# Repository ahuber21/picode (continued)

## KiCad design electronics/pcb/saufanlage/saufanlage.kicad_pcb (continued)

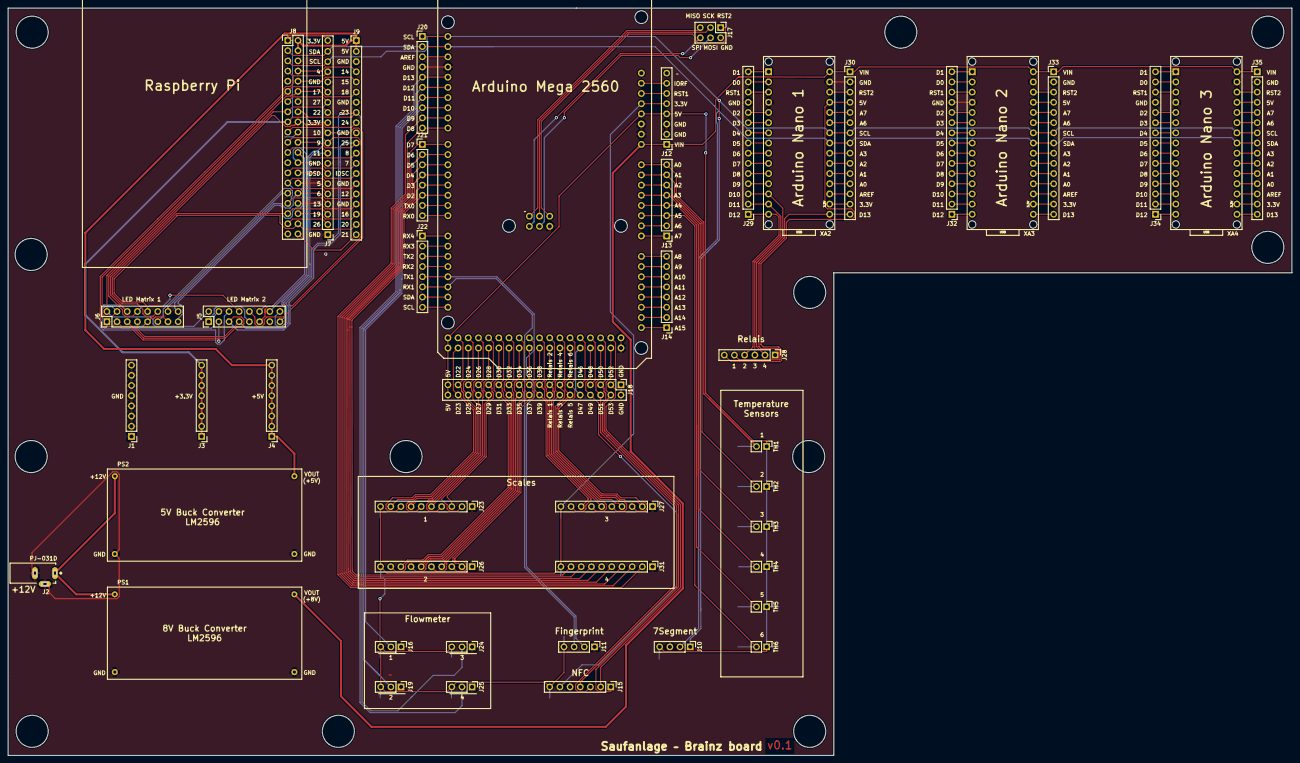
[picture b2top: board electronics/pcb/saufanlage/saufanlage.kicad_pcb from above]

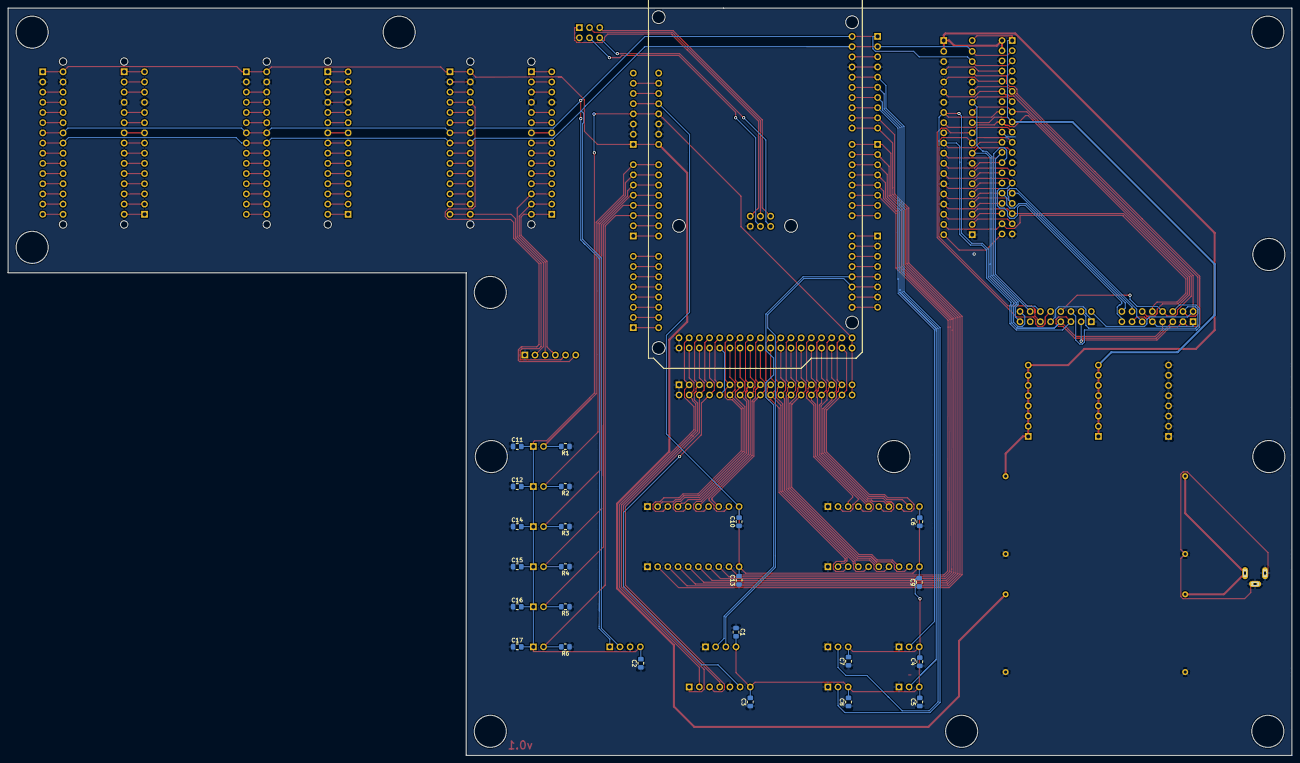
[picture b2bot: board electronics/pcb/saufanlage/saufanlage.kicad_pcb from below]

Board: 2 copper layers, 320.3 x 186.4 mm, 70 parts (24 on the bottom side), 188 nets.

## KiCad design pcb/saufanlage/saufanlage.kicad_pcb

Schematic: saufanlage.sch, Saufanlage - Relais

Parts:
C1: C; C_2220_5650Metric_Pad1.97x5.40mm_HandSolder
C2: C; C_1206_3216Metric_Pad1.42x1.75mm_HandSolder
C3: C; C_0805_2012Metric_Pad1.15x1.40mm_HandSolder
C4: C; C_1812_4532Metric_Pad1.30x3.40mm_HandSolder
D1: D_Schottky; D_SOT-23_ANK
D2: LED; LED_0805_2012Metric_Pad1.15x1.40mm_HandSolder
J1: Screw_Terminal_01x02; TerminalBlock_Altech_AK300-2_P5.00mm
J2: Conn_02x06_Odd_Even; IDC-Header_2x06_P2.54mm_Vertical
J3: Conn_01x02_Female; PinSocket_1x02_P2.54mm_Vertical
J4: Conn_01x07_Male; JST_EH_B7B-EH-A_1x07_P2.50mm_Vertical
J5: Conn_02x20_Odd_Even; PinSocket_2x20_P2.54mm_Vertical
J6: Conn_01x06_Female; PinSocket_1x06_P2.54mm_Vertical
J7, J8, J9, J10: Conn_01x03_Male; FanPinHeader_1x03_P2.54mm_Vertical
L1: L; L_12x12mm_H8mm
R1, R2, R3, R4, R5, R6, R7, R8, R9, R10, R11: R; R_0805_2012Metric_Pad1.15x1.40mm_HandSolder
SW1: SW_Push; SW_SPST_CK_RS282G05A3
U1: BD9G341EFJ; HTSOP-8-1EP_3.9x4.9mm_P1.27mm_EP2.4x3.2mm_ThermalVias
U2: 74HC595; DIP-16_W7.62mm_Socket

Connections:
+3V3: J4.2, J4.6, J5.1, J7.3, J8.3, J9.3, J10.3
+5V: C4.1, J5.2, J6.1, L1.2, R6.1, R9.1, SW1.1, U2.16
+12V: C1.1, J1.2, R1.1, U1.8 (VCC)
GND: C1.2, C4.2, D1.2 (A), D2.1, J1.1, J3.2, J4.5, J5.9, J6.6, J7.1, J8.1, J9.1, J10.1, R2.2, R3.2, R4.2, R5.1, R7.2, R8.1, R10.1, R11.1, U1.2 (GND), U2.8, U2.13
unnamed: C2.1, U1.3 (VC)
unnamed: C2.2, R4.1
unnamed: C3.1, U1.7 (BST)
unnamed: C3.2, D1.1 (K), L1.1, U1.1 (LX)
unnamed: D2.2, R9.2
unnamed: J2.1, U2.4
unnamed: J2.2, U2.3
unnamed: J2.3, U2.7
unnamed: J2.4, U2.2
unnamed: J2.5, U2.6
unnamed: J2.6, R8.2
unnamed: J2.7, U2.1
unnamed: J2.8, R10.2
unnamed: J2.9, R5.2
unnamed: J2.10, U2.5
unnamed: J2.11, U2.15
unnamed: J2.12, R11.2
unnamed: J3.1, SW1.2
unnamed: J4.3, J5.10
unnamed: J4.4, J5.8
unnamed: J5.16, U2.11
unnamed: J5.18, U2.12
unnamed: J5.22, U2.14
unnamed: J5.32, J6.2
unnamed: J5.33, J9.2
unnamed: J5.35, J8.2
unnamed: J5.36, J6.3
unnamed: J5.37, J7.2
unnamed: J5.38, J6.4
unnamed: J5.40, J6.5
unnamed: J5.31, J10.2
unnamed: R1.2, R2.1, U1.6 (EN)
unnamed: R3.1, U1.5 (RT)
unnamed: R6.2, R7.1, U1.4 (FB)

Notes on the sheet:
Buck Converter
Flowmeter-connection
Relais-Connection
Raspberry - reset
Fingerprint Connection
7-seg anzeige

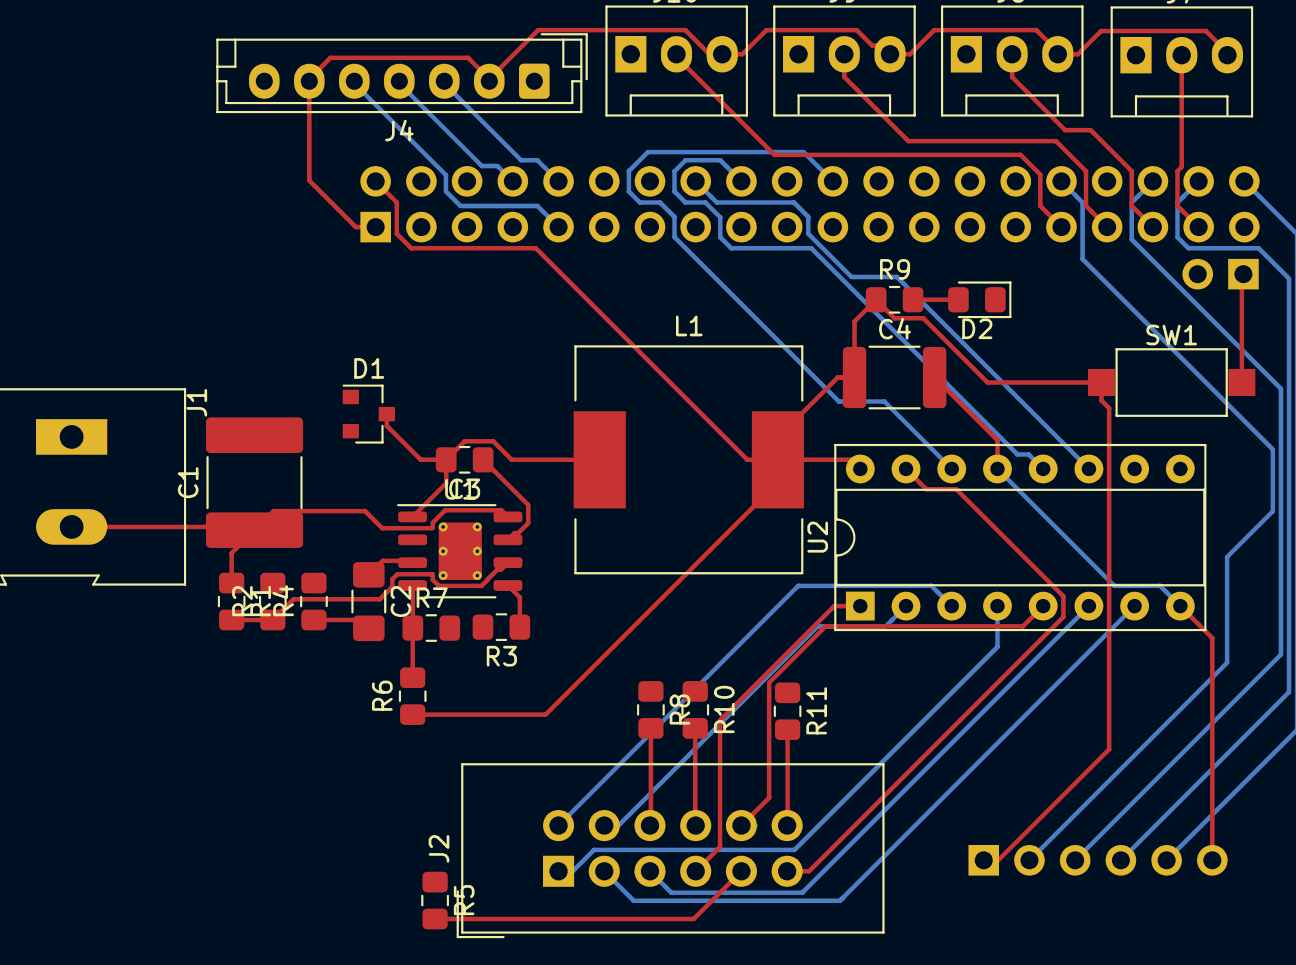
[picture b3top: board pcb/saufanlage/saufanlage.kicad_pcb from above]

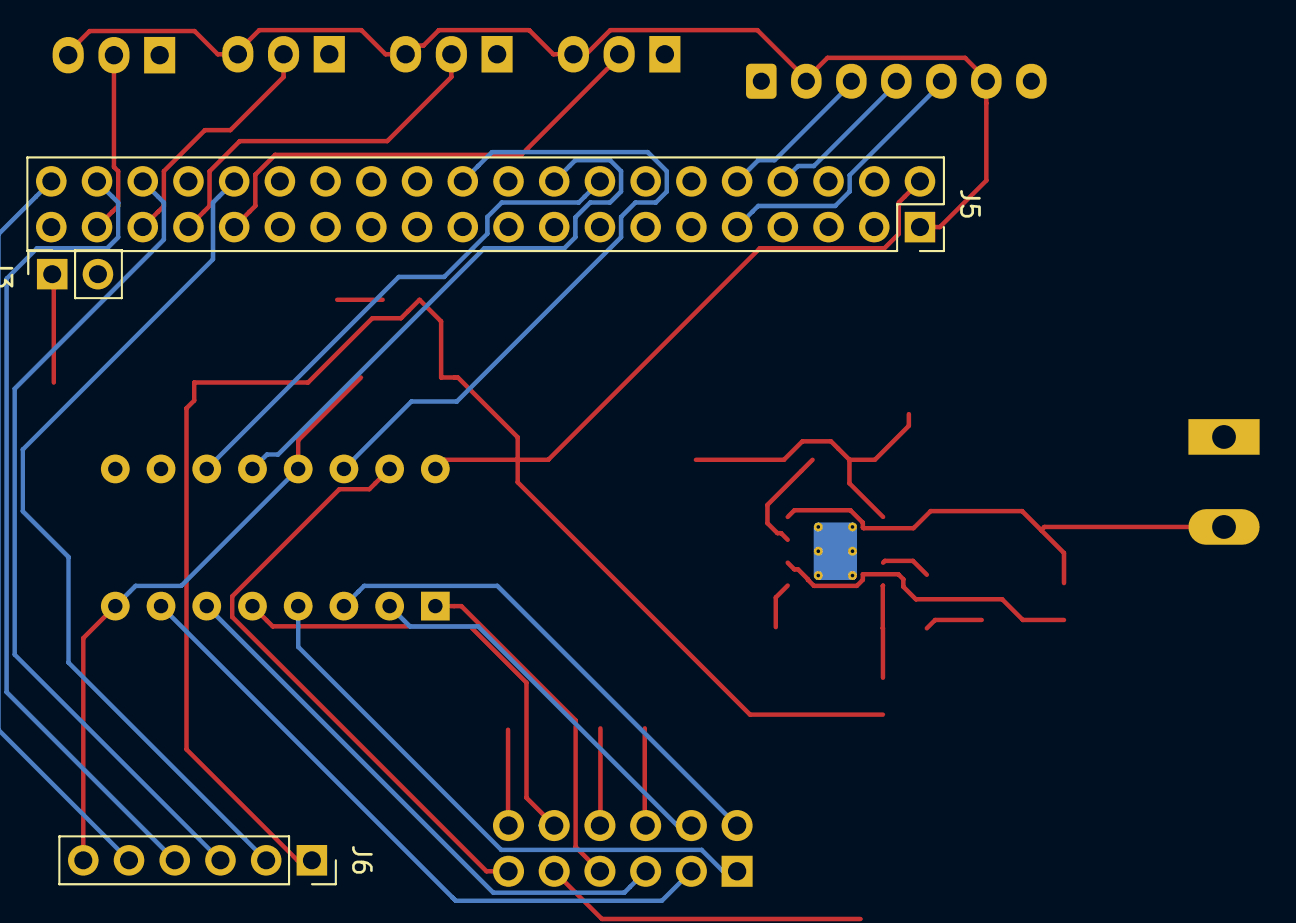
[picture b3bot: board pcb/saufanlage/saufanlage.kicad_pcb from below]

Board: 2 copper layers, 31 parts (3 on the bottom side), 38 nets.

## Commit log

2019-02-23 Add LICENSE
2019-02-23 Add switcher flask app with dummy slide button
2019-02-24 Rename switcherapp -> app
2019-02-24 Add config
2019-02-24 Add missing static files
2019-02-24 Save switch states to disk
2019-02-25 Update URL
2019-03-09 Add RGB Matrix driver as submodule
2019-04-01 Add flowmeter
2019-04-28 Add FPM-C and FPM-pi
2019-04-28 Add wiring to README
2019-04-28 Remove last line
2019-04-29 Modified readme to complete the UART config.
2019-05-08 Add pyfingerprint example code
2019-05-12 Update README.md -- completed and updated primary setup
2019-05-25 Add daemon
2019-05-31 It's alive!
2019-06-02 Last octopi commit :spaceship:
2019-06-02 Update switchstates
2019-06-04 Cleanup repo :paperclip:
2019-06-04 Start playing with User and Fingerprint classes
2019-06-04 Add Pi-Zero-Pinout
2019-06-06 Debug usermanager
2019-06-06 Add four digit display
2019-06-12 Added first draft of Circuit Board
2019-12-03 Add some stuff for electronics
2019-12-03 Add layout idea
2020-01-07 Update electronics stuff
2020-01-08 Saufanlagen PCB update
2020-01-09 Add connectors
2020-01-12 Backup commit
2020-01-12 Label Flowmeter
2020-01-14 More brainz updates
2020-02-10 Add fourth scale and temp sensor
2020-02-10 Add I2C 7 Segment test
2020-03-18 Add temperature sensors
2020-03-19 Clean up tracks
2020-03-19 Add caps
2020-08-17 Post Roggenburg 2020 commit
